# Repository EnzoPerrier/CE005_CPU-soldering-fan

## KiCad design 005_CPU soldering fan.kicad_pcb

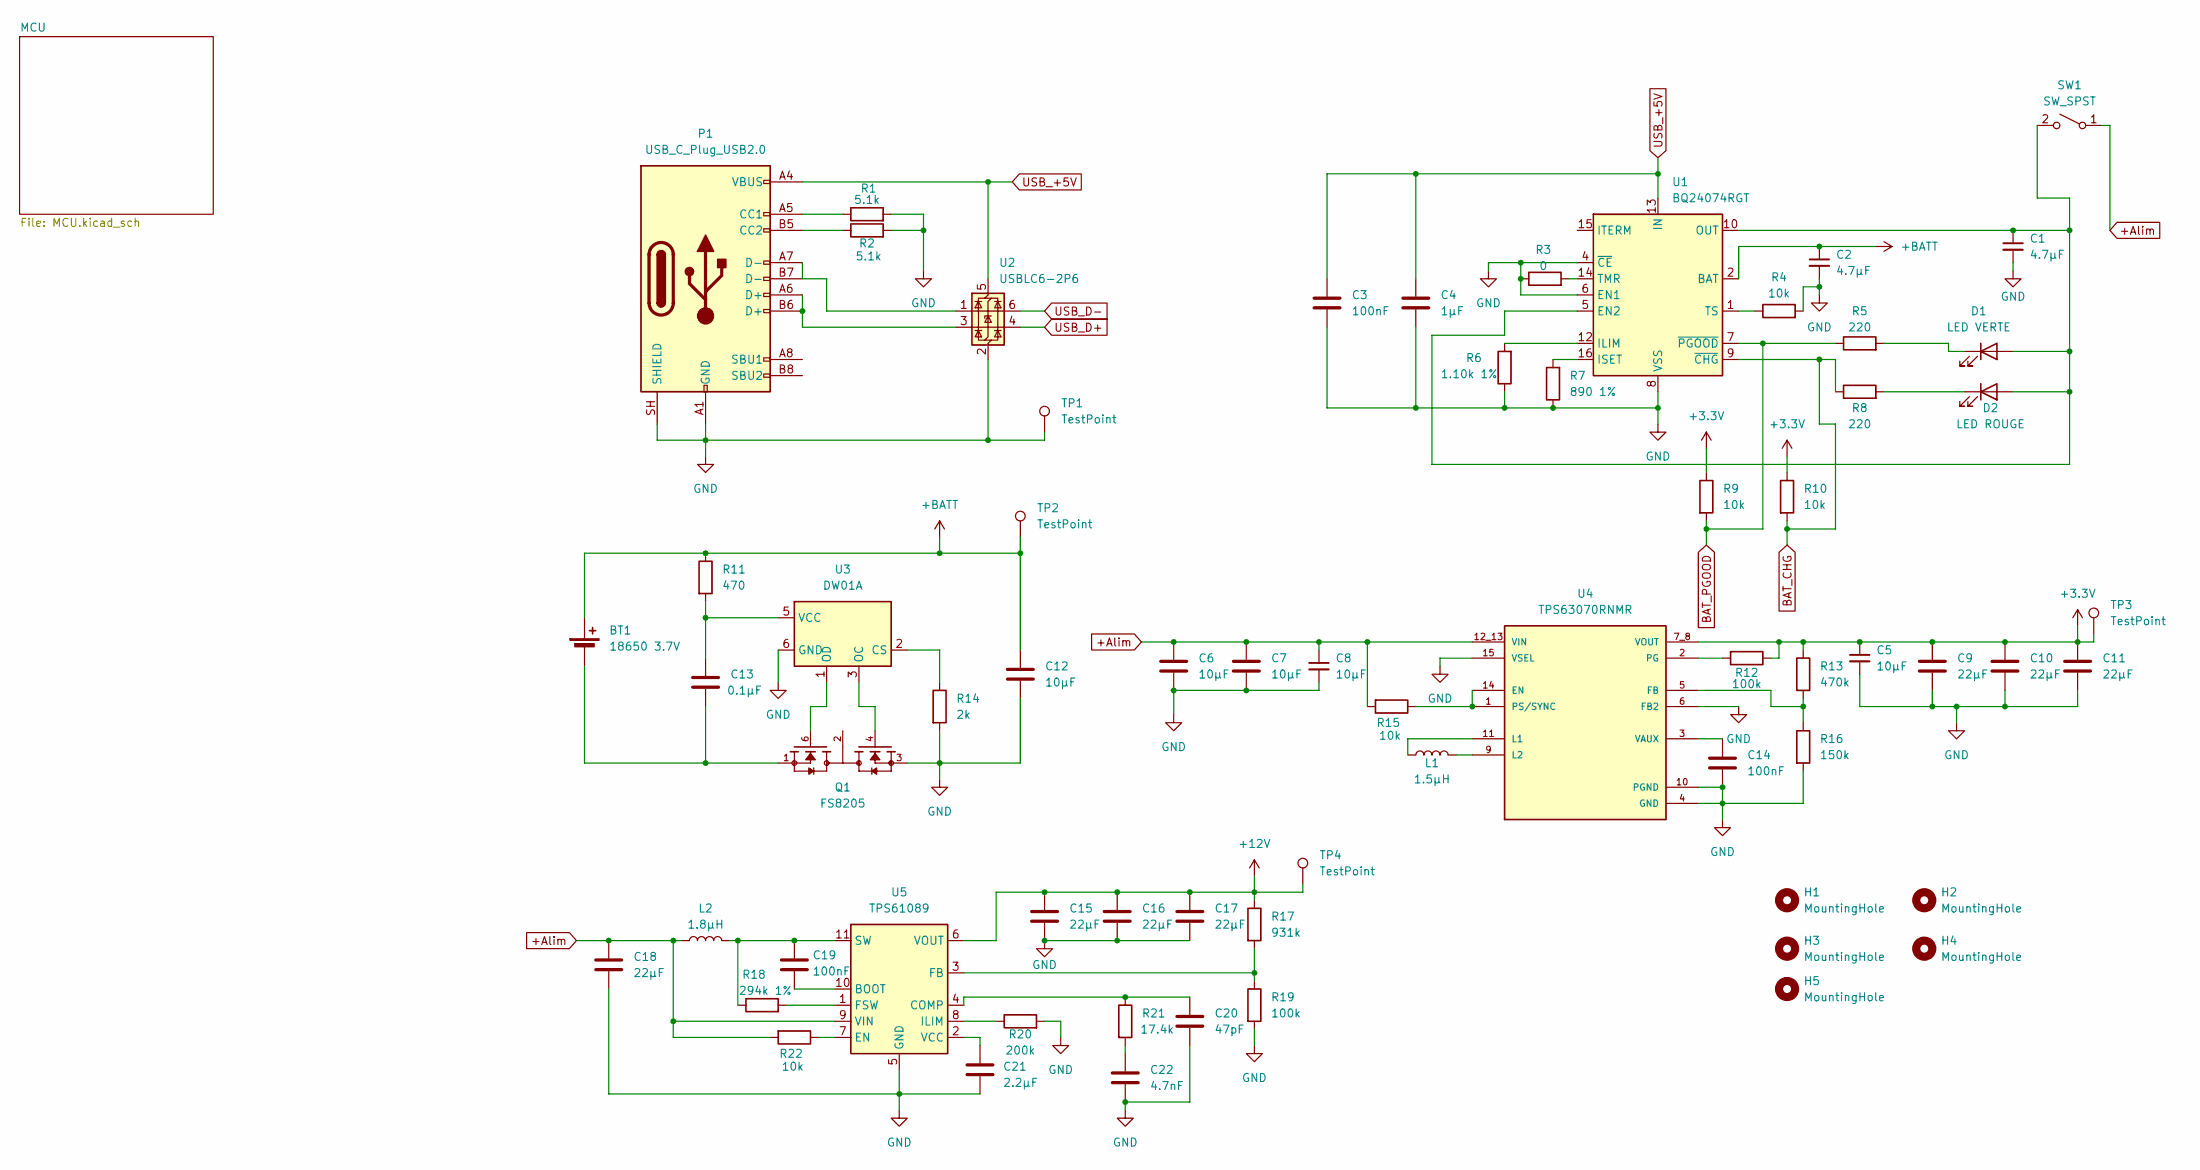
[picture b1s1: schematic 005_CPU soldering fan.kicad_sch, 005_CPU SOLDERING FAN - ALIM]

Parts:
BT1: 18650 3.7V; SolderWire-0.75sqmm_1x02_P4.8mm_D1.25mm_OD2.3mm
C1, C2: 4.7µF; C_0805_2012Metric
C3, C19: 100nF; C_0805_2012Metric
C4: 1µF; C_1206_3216Metric
C5, C8: 10µF; C_0603_1608Metric
C6, C7: 10µF; C_0805_2012Metric
C9, C10, C11, C15, C16, C17, C18: 22µF; C_1210_3225Metric
C12: 10µF; C_1210_3225Metric
C13: 0.1µF; C_0805_2012Metric
C14: 100nF; C_0603_1608Metric
C20: 47pF; C_0805_2012Metric
C21: 2.2µF; C_0805_2012Metric
C22: 4.7nF; C_0805_2012Metric
D1: LED VERTE; LED_1206_3216Metric
D2: LED ROUGE; LED_1206_3216Metric
H1, H2, H3, H4, H5: MountingHole; MountingHole_3.2mm_M3_DIN965_Pad_TopBottom
L1: 1.5µH; IND_XFL4020-152MEC
L2: 1.8µH; IND_CDMC8D28NP1R8MC
P1: USB_C_Plug_USB2.0; USB_C_Receptacle_GCT_USB4105-xx-A_16P_TopMnt_Horizontal
Q1: FS8205; SOT95P280X145-6N; PARTREV 1.9
R1, R2: 5.1k; R_0805_2012Metric
R3: 0; R_0805_2012Metric
R4, R9, R10, R15, R22: 10k; R_0805_2012Metric
R5, R8: 220; R_0805_2012Metric
R6: 1.10k 1%; R_0805_2012Metric
R7: 890 1%; R_0805_2012Metric
R11: 470; R_0805_2012Metric
R12, R19: 100k; R_0805_2012Metric
R13: 470k; R_0805_2012Metric
R14: 2k; R_0805_2012Metric
R16: 150k; R_0805_2012Metric
R17: 931k; R_0805_2012Metric
R18: 294k 1%; R_0805_2012Metric
R20: 200k; R_0805_2012Metric
R21: 17.4k; R_0805_2012Metric
SW1: SW_SPST; JST_EH_B2B-EH-A_1x02_P2.50mm_Vertical
TP1: TestPoint; TestPoint_Pad_1.0x1.0mm
TP2, TP3, TP4: TestPoint; TestPoint_Pad_D1.0mm
U1: BQ24074RGT; VQFN-16-1EP_3x3mm_P0.5mm_EP1.6x1.6mm
U2: USBLC6-2P6; SOT-666
U3: DW01A; SOT-23-6
U4: TPS63070RNMR; VREG_TPS63070RNMR; PARTREV B
U5: TPS61089; Texas_VQFN-RNR0011A-11

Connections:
+3.3V: C5.1, C9.1, C10.1, C11.1, R9.1, R10.1, R12.1, R13.1, TP3.1 (1_1), U4.7_8 (VOUT); also elsewhere on the board
+12V: C15.1, C16.1, C17.1, R17.1, TP4.1 (1_1), U5.6 (VOUT); also elsewhere on the board
+Alim: C6.1, C7.1, C8.1, C18.1, L2.1, R15.2, R22.2, SW1.1 (A), U4.12_13 (VIN), U5.9 (VIN); also elsewhere on the board
+BATT: BT1.1 (+), C2.1, C12.1, R11.1, TP2.1 (1_1), U1.2 (BAT), U1.3 (BAT); also elsewhere on the board
BAT_CHG: R8.1, R10.2, U1.9 (~CHG)
BAT_PGOOD: R5.1, R9.2, U1.7 (~PGOOD)
GND: C1.2, C2.2, C3.2, C4.2, C5.2, C6.2, C7.2, C8.2, C9.2, C10.2, C11.2, C12.2, C14.2, C15.2, C16.2, C17.2, C18.2, C20.2, C21.2, C22.2, P1.A1 (GND), P1.A12 (GND), P1.B1 (GND), P1.B12 (GND), P1.SH (SHIELD), Q1.3, R1.2, R2.2, R3.1, R4.2, R6.1, R7.1, R14.2, R16.2, R19.2, R20.2, TP1.1 (1_1), U1.4 (~CE), U1.6 (EN1), U1.8 (VSS), U1.17 (VSS), U2.2 (GND), U3.6 (GND), U4.4 (GND), U4.6 (FB2), U4.10 (PGND), U4.15 (VSEL), U5.5 (GND); also elsewhere on the board
unnamed: BT1.2 (-), C13.2, Q1.1
unnamed: C22.1, R21.2
unnamed: C1.1, D1.2 (A), D2.2 (A), SW1.2 (B), U1.5 (EN2), U1.10 (OUT), U1.11 (OUT)
unnamed: D1.1 (K), R5.2
unnamed: D2.1 (K), R8.2
unnamed: P1.A5 (CC1), R1.1
unnamed: P1.B5 (CC2), R2.1
unnamed: P1.A6 (D+), P1.B6 (D+), U2.3 (I/O2)
unnamed: P1.A7 (D-), P1.B7 (D-), U2.1 (I/O1)
unnamed: Q1.2, Q1.5
unnamed: R6.2, U1.12 (ILIM)
unnamed: R7.2, U1.16 (ISET)
unnamed: R3.2, U1.14 (TMR)
unnamed: R4.1, U1.1 (TS)
unnamed: R14.1, U3.2 (CS)
unnamed: Q1.4, U3.3 (OC)
unnamed: Q1.6, U3.1 (OD)
unnamed: C13.1, R11.2, U3.5 (VCC)
unnamed: R15.1, U4.1 (PS/SYNC), U4.14 (EN)
unnamed: R13.2, R16.1, U4.5 (FB)
unnamed: L1.1, U4.11 (L1)
unnamed: L1.2, U4.9 (L2)
unnamed: R12.2, U4.2 (PG)
unnamed: C14.1, U4.3 (VAUX)
unnamed: C19.2, U5.10 (BOOT)
unnamed: C20.1, R21.1, U5.4 (COMP)
unnamed: R22.1, U5.7 (EN)
unnamed: R17.2, R19.1, U5.3 (FB)
unnamed: R18.2, U5.1 (FSW)
unnamed: R20.1, U5.8 (ILIM)
unnamed: C19.1, L2.2, R18.1, U5.11 (SW)
unnamed: C21.1, U5.2 (VCC)
USB_+5V: C3.1, C4.1, P1.A4 (VBUS), P1.A9 (VBUS), P1.B4 (VBUS), P1.B9 (VBUS), U1.13 (IN), U2.5 (VBUS)
USB_D+: U2.4 (I/O2); also elsewhere on the board
USB_D-: U2.6 (I/O1); also elsewhere on the board

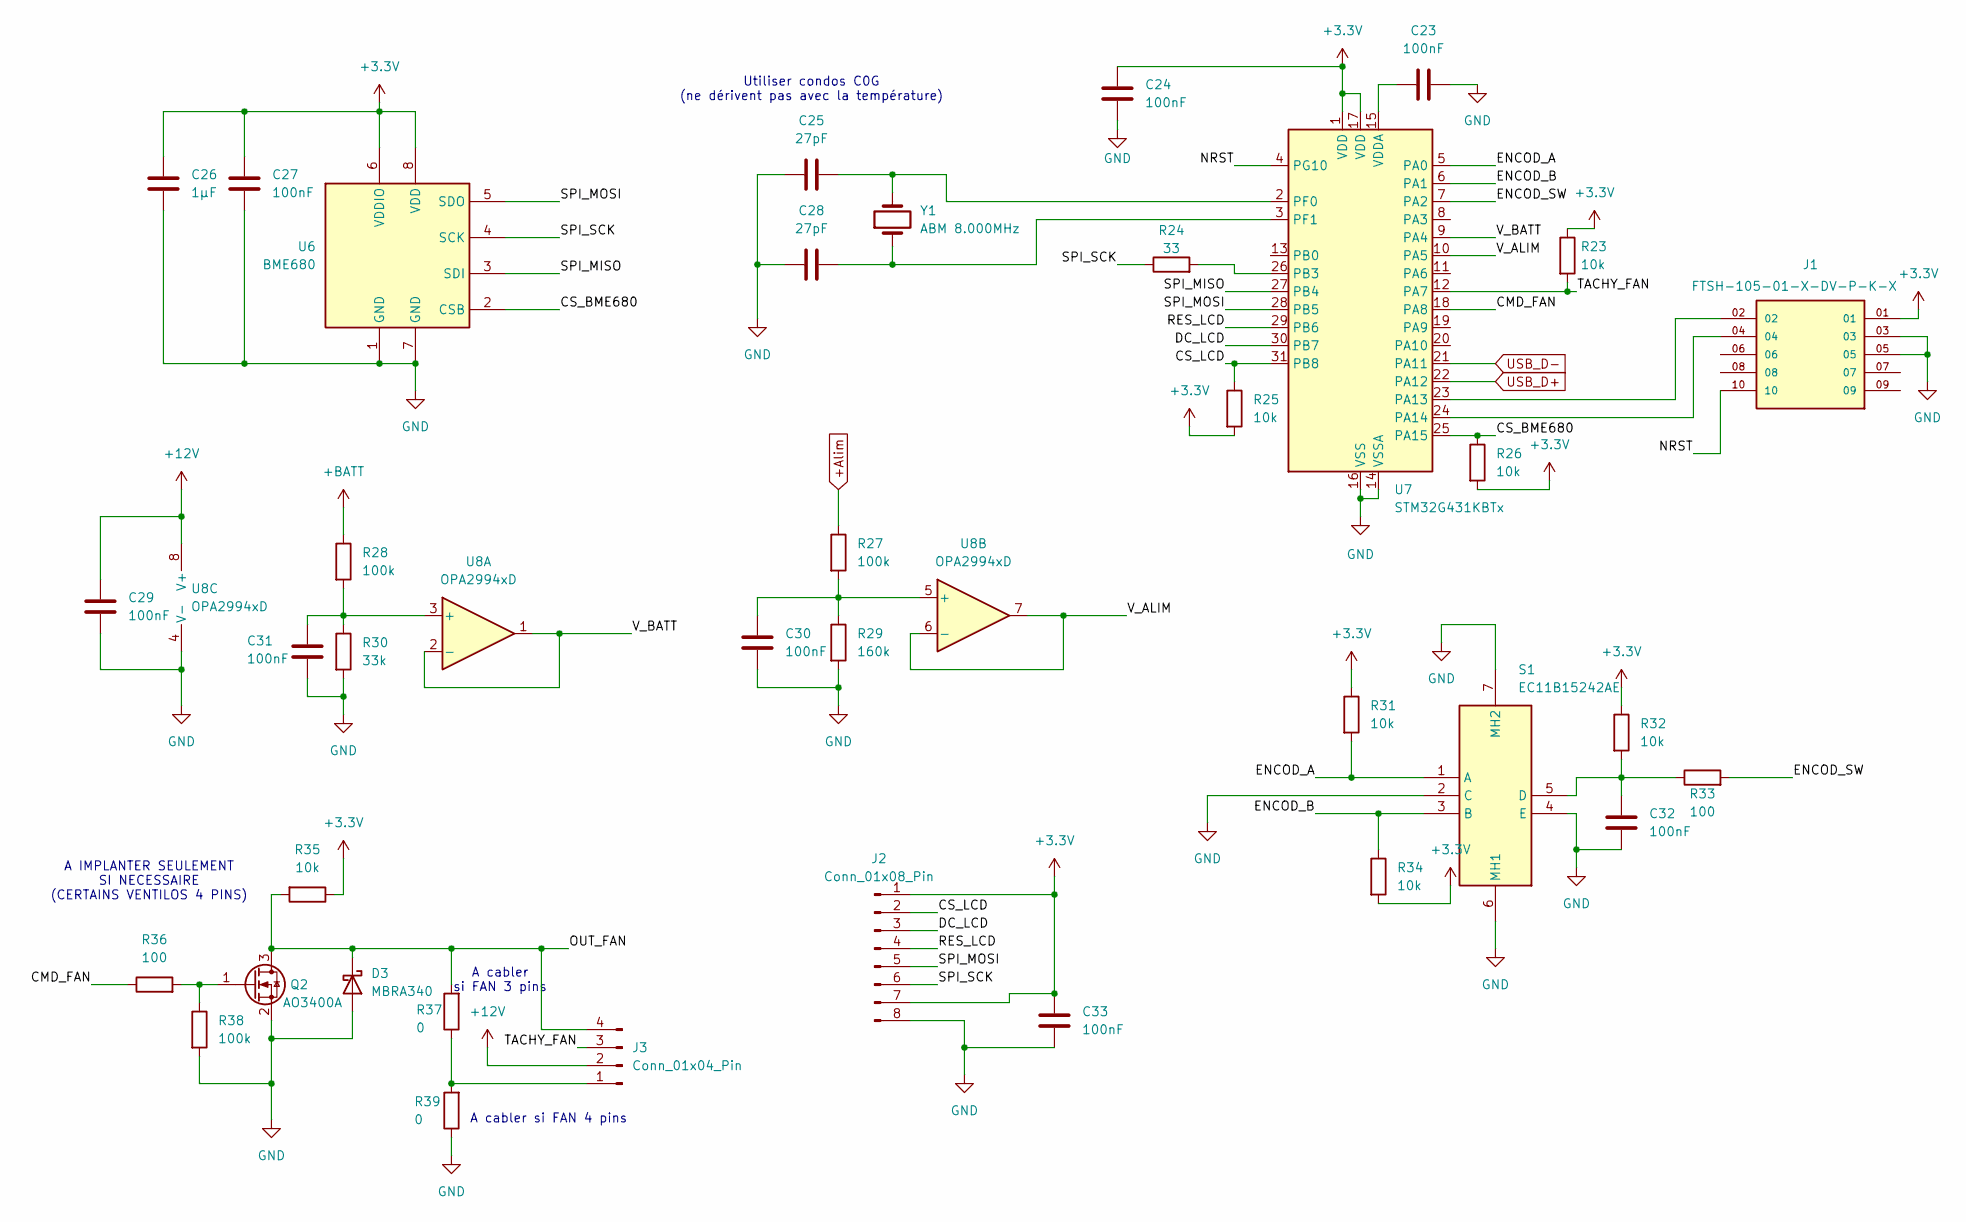
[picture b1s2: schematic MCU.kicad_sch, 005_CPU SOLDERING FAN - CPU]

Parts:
C23, C24, C27, C29, C30, C31, C32, C33: 100nF; C_0805_2012Metric
C25, C28: 27pF; C_0805_2012Metric
C26: 1µF; C_0805_2012Metric
D3: MBRA340; D_SMA
J1: FTSH-105-01-X-DV-P-K-X; SAMTEC_FTSH-105-01-X-DV-P-K-X; PARTREV H
J2: Conn_01x08_Pin; JST_EH_B8B-EH-A_1x08_P2.50mm_Vertical
J3: Conn_01x04_Pin; PinHeader_1x04_P2.54mm_Vertical
Q2: AO3400A; SOT-23
R23, R25, R26, R31, R32, R34, R35: 10k; R_0805_2012Metric
R24: 33; R_0805_2012Metric
R27, R28, R38: 100k; R_0805_2012Metric
R29: 160k; R_0805_2012Metric
R30: 33k; R_0805_2012Metric
R33, R36: 100; R_0805_2012Metric
R37, R39: 0; R_1210_3225Metric
S1: EC11B15242AE; Manufacturer_Part_Number EC11B15242AE; Mouser Part Number 688-EC11B15242AE
U6: BME680; Bosch_LGA-8_3x3mm_P0.8mm_ClockwisePinNumbering
U7: STM32G431KBTx; LQFP-32_7x7mm_P0.8mm
U8: OPA2994xD; SOIC-8_3.9x4.9mm_P1.27mm
Y1: ABM 8.000MHz; Crystal_SMD_Abracon_ABM3-2Pin_5.0x3.2mm_HandSoldering

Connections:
+3.3V: C24.1, C26.1, C27.1, C33.1, J1.01, J2.1, J2.7, R23.1, R25.2, R26.2, R31.1, R32.1, R34.2, R35.1, U6.6 (VDDIO), U6.8 (VDD), U7.1 (VDD), U7.17 (VDD); also elsewhere on the board
+12V: C29.1, J3.2, U8.8 (V+); also elsewhere on the board
+Alim: R27.1; also elsewhere on the board
+BATT: R28.1; also elsewhere on the board
/MCU/CMD_FAN: R36.1, U7.18 (PA8)
/MCU/CS_BME680: R26.1, U6.2 (CSB), U7.25 (PA15)
/MCU/CS_LCD: J2.2, R25.1, U7.31 (PB8)
/MCU/DC_LCD: J2.3, U7.30 (PB7)
/MCU/ENCOD_A: R31.2, S1.1 (A), U7.5 (PA0)
/MCU/ENCOD_B: R34.1, S1.3 (B), U7.6 (PA1)
/MCU/ENCOD_SW: R33.2, U7.7 (PA2)
/MCU/NRST: J1.10, U7.4 (PG10)
/MCU/OUT_FAN: D3.1 (K), J3.4, Q2.3 (D), R35.2, R37.2
/MCU/RES_LCD: J2.4, U7.29 (PB6)
/MCU/SPI_MISO: U6.3 (SDI), U7.27 (PB4)
/MCU/SPI_MOSI: J2.5, U6.5 (SDO), U7.28 (PB5)
/MCU/SPI_SCK: J2.6, R24.1, U6.4 (SCK)
/MCU/TACHY_FAN: J3.3, R23.2, U7.12 (PA7)
/MCU/V_ALIM: U7.10 (PA5), U8.6 (-), U8.7
/MCU/V_BATT: U7.9 (PA4), U8.1, U8.2 (-)
GND: C23.2, C24.2, C25.1, C26.2, C27.2, C28.1, C29.2, C30.2, C31.2, C32.2, C33.2, D3.2 (A), J1.03, J1.05, J2.8, Q2.2 (S), R29.2, R30.2, R38.2, R39.1, S1.2 (C), S1.4 (E), S1.6 (MH1), S1.7 (MH2), U6.1 (GND), U6.7 (GND), U7.14 (VSSA), U7.16 (VSS), U7.32 (VSS), U8.4 (V-); also elsewhere on the board
unnamed: J3.1, R37.1, R39.2
unnamed: Q2.1 (G), R36.2, R38.1
unnamed: C32.1, R32.2, R33.1, S1.5 (D)
unnamed: J1.02, U7.23 (PA13)
unnamed: J1.04, U7.24 (PA14)
unnamed: R24.2, U7.26 (PB3)
unnamed: C25.2, U7.2 (PF0), Y1.2
unnamed: C28.2, U7.3 (PF1), Y1.1
unnamed: C23.1, U7.15 (VDDA)
unnamed: C31.1, R28.2, R30.1, U8.3 (+)
unnamed: C30.1, R27.2, R29.1, U8.5 (+)
USB_D+: U7.22 (PA12); also elsewhere on the board
USB_D-: U7.21 (PA11); also elsewhere on the board

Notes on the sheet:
Utiliser condos C0G (ne dérivent pas avec la température)
A cabler si FAN 4 pins
A cabler si FAN 3 pins
A IMPLANTER SEULEMENT SI NECESSAIRE (CERTAINS VENTILOS 4 PINS)

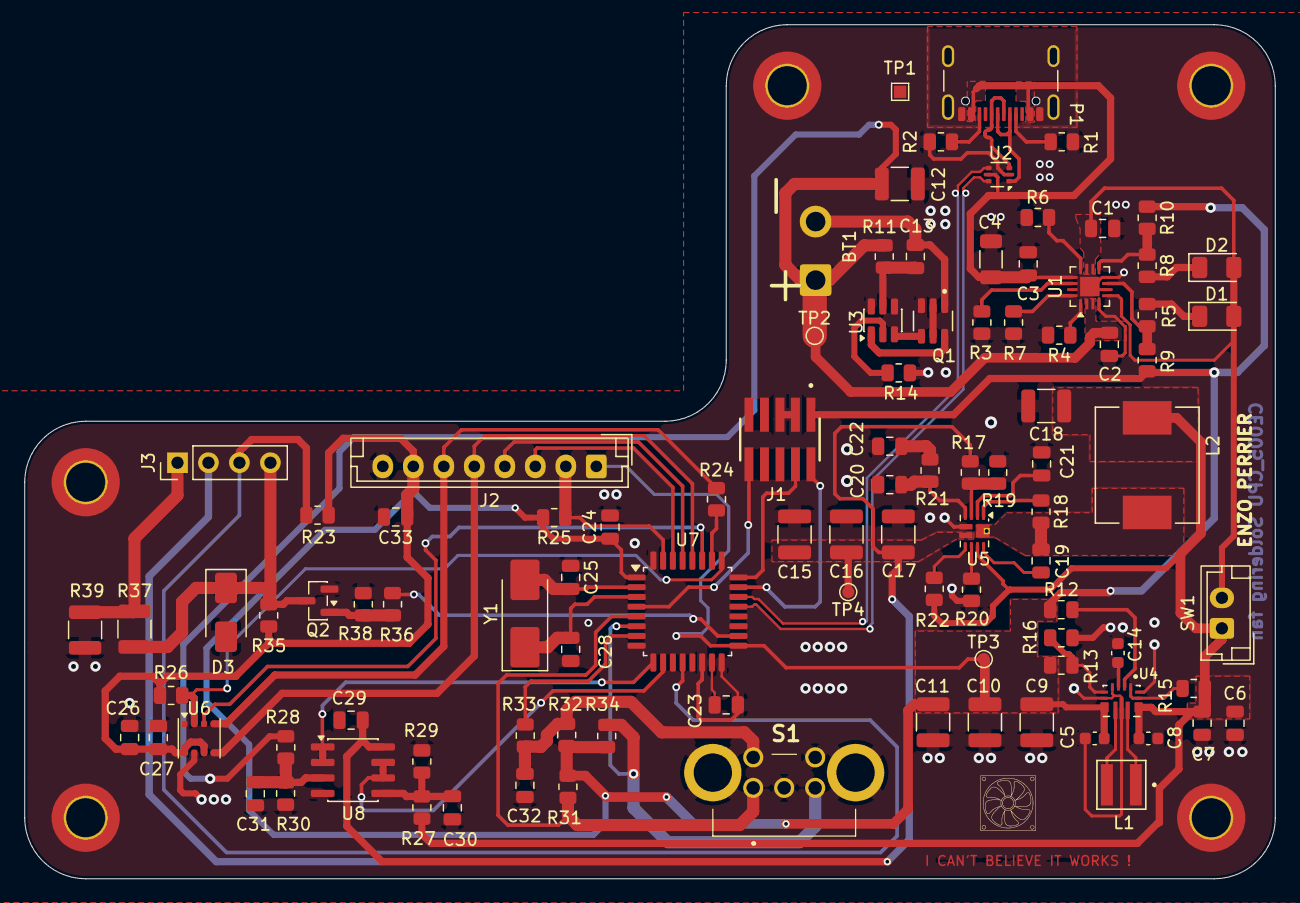
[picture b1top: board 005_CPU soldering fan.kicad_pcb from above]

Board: 2 copper layers, 102.5 x 70.0 mm, 104 parts (0 on the bottom side), 69 nets.

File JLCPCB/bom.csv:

Designator,Footprint,Quantity,Value,LCSC Part #
"C1, C2",0805,2,4.7µF,
"C10, C11, C15, C16, C17, C18, C9",1210,7,22µF,
C12,1210,1,10µF,
C13,0805,1,0.1µF,
C14,0603,1,100nF,
"C19, C23, C24, C27, C29, C3, C30, C31, C32, C33",0805,10,100nF,
C20,0805,1,47pF,
C21,0805,1,2.2µF,
C22,0805,1,4.7nF,
"C25, C28",0805,2,27pF,
C26,0805,1,1µF,
C4,1206,1,1µF,
"C5, C8",0603,2,10µF,
"C6, C7",0805,2,10µF,
D1,1206,1,LED VERTE,
D2,1206,1,LED ROUGE,
D3,D_SMA,1,MBRA340,
J1,SAMTEC_FTSH-105-01-X-DV-P-K-X,1,FTSH-105-01-X-DV-P-K-X,
J2,JST_EH_B8B-EH-A_1x08_P2.50mm_Vertical,1,Conn_01x08_Pin,
J3,PinHeader_1x04_P2.54mm_Vertical,1,Conn_01x04_Pin,
L1,IND_XFL4020-152MEC,1,1.5µH,
L2,IND_CDMC8D28NP1R8MC,1,1.8µH,
P1,USB_C_Receptacle_GCT_USB4105-xx-A_16P_TopMnt_Horizontal,1,USB_C_Plug_USB2.0,
Q1,SOT95P280X145-6N,1,FS8205,
Q2,SOT-23,1,AO3400A,
"R1, R2",0805,2,5.1k,
"R10, R15, R22, R23, R25, R26, R31, R32, R34, R35, R4, R9",0805,12,10k,
R11,0805,1,470,
"R12, R19, R27, R28, R38",0805,5,100k,
R13,0805,1,470k,
R14,0805,1,2k,
R16,0805,1,150k,
R17,0805,1,931k,
R18,0805,1,294k 1%,
R20,0805,1,200k,
R21,0805,1,17.4k,
R24,0805,1,33,
R29,0805,1,160k,
R3,0805,1,0,
R30,0805,1,33k,
"R33, R36",0805,2,100,
"R37, R39",1210,2,0,
"R5, R8",0805,2,220,
R6,0805,1,1.10k 1%,
R7,0805,1,890 1%,
U1,VQFN-16-1EP_3x3mm_P0.5mm_EP1.6x1.6mm,1,BQ24074RGT,
U2,SOT-666,1,USBLC6-2P6,
U3,SOT-23-6,1,DW01A,
U4,VREG_TPS63070RNMR,1,TPS63070RNMR,
U5,Texas_VQFN-RNR0011A-11,1,TPS61089,
U6,Bosch_LGA-8_3x3mm_P0.8mm_ClockwisePinNumbering,1,BME680,
U7,LQFP-32_7x7mm_P0.8mm,1,STM32G431KBTx,
U8,SOIC-8_3.9x4.9mm_P1.27mm,1,OPA2994xD,
Y1,Crystal_SMD_Abracon_ABM3-2Pin_5.0x3.2mm_HandSoldering,1,ABM 8.000MHz,

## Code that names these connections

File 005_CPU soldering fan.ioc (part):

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Mcu.Name=STM32G431K(6-8-B)Tx
Mcu.Package=LQFP32
Mcu.UserName=STM32G431KBTx
PA0.GPIOParameters=GPIO_Label
PA0.GPIO_Label=ENCOD_A
PA0.Signal=S_TIM2_CH1
PA1.GPIOParameters=GPIO_Label
PA1.GPIO_Label=ENCOD_B
PA1.Signal=S_TIM2_CH2
PA11.Mode=Device
PA11.Signal=USB_DM
PA12.Mode=Device
PA12.Signal=USB_DP
PA13.Mode=Serial_Wire
PA13.Signal=SYS_JTMS-SWDIO
PA14.Mode=Serial_Wire
PA14.Signal=SYS_JTCK-SWCLK
PA15.GPIOParameters=GPIO_Label
PA15.GPIO_Label=CS_BME680
PA15.Signal=GPIO_Output
PA2.GPIOParameters=GPIO_Label
PA2.GPIO_Label=ENCOD_SW
PA2.Signal=GPIO_Input
PA4.GPIOParameters=GPIO_Label
PA4.GPIO_Label=V_BATT
PA4.Mode=IN17-Single-Ended
PA4.Signal=ADC2_IN17
PA5.GPIOParameters=GPIO_Label
PA5.GPIO_Label=V_ALIM
PA5.Mode=IN13-Single-Ended
PA5.Signal=ADC2_IN13
PA7.GPIOParameters=GPIO_Label
PA7.GPIO_Label=TACHY_FAN
PA7.Signal=S_TIM3_CH2
PA8.GPIOParameters=GPIO_Label
PA8.GPIO_Label=CMD_FAN
PA8.Signal=S_TIM1_CH1
PB3.GPIOParameters=GPIO_Label
PB3.GPIO_Label=SPI_SCK
PB3.Mode=Full_Duplex_Master
PB3.Signal=SPI1_SCK
PB4.GPIOParameters=GPIO_Label
PB4.GPIO_Label=SPI_MISO
PB4.Mode=Full_Duplex_Master
PB4.Signal=SPI1_MISO
PB5.GPIOParameters=GPIO_Label
PB5.GPIO_Label=SPI_MOSI
PB5.Mode=Full_Duplex_Master
PB5.Signal=SPI1_MOSI
PB6.GPIOParameters=GPIO_Label
PB6.GPIO_Label=RES_LCD
PB6.Signal=GPIO_Output
PB7.GPIOParameters=GPIO_Label
PB7.GPIO_Label=DC_LCD
PB7.Signal=GPIO_Output
PB8-BOOT0.GPIOParameters=GPIO_Label
PB8-BOOT0.GPIO_Label=CS_LCD
PB8-BOOT0.Signal=GPIO_Output
PF0-OSC_IN.Mode=HSE-External-Oscillator
PF0-OSC_IN.Signal=RCC_OSC_IN
PF1-OSC_OUT.Mode=HSE-External-Oscillator
PF1-OSC_OUT.Signal=RCC_OSC_OUT
RCC.HSE_VALUE=8000000
RCC.SYSCLKFreq_VALUE=16000000
board=custom
